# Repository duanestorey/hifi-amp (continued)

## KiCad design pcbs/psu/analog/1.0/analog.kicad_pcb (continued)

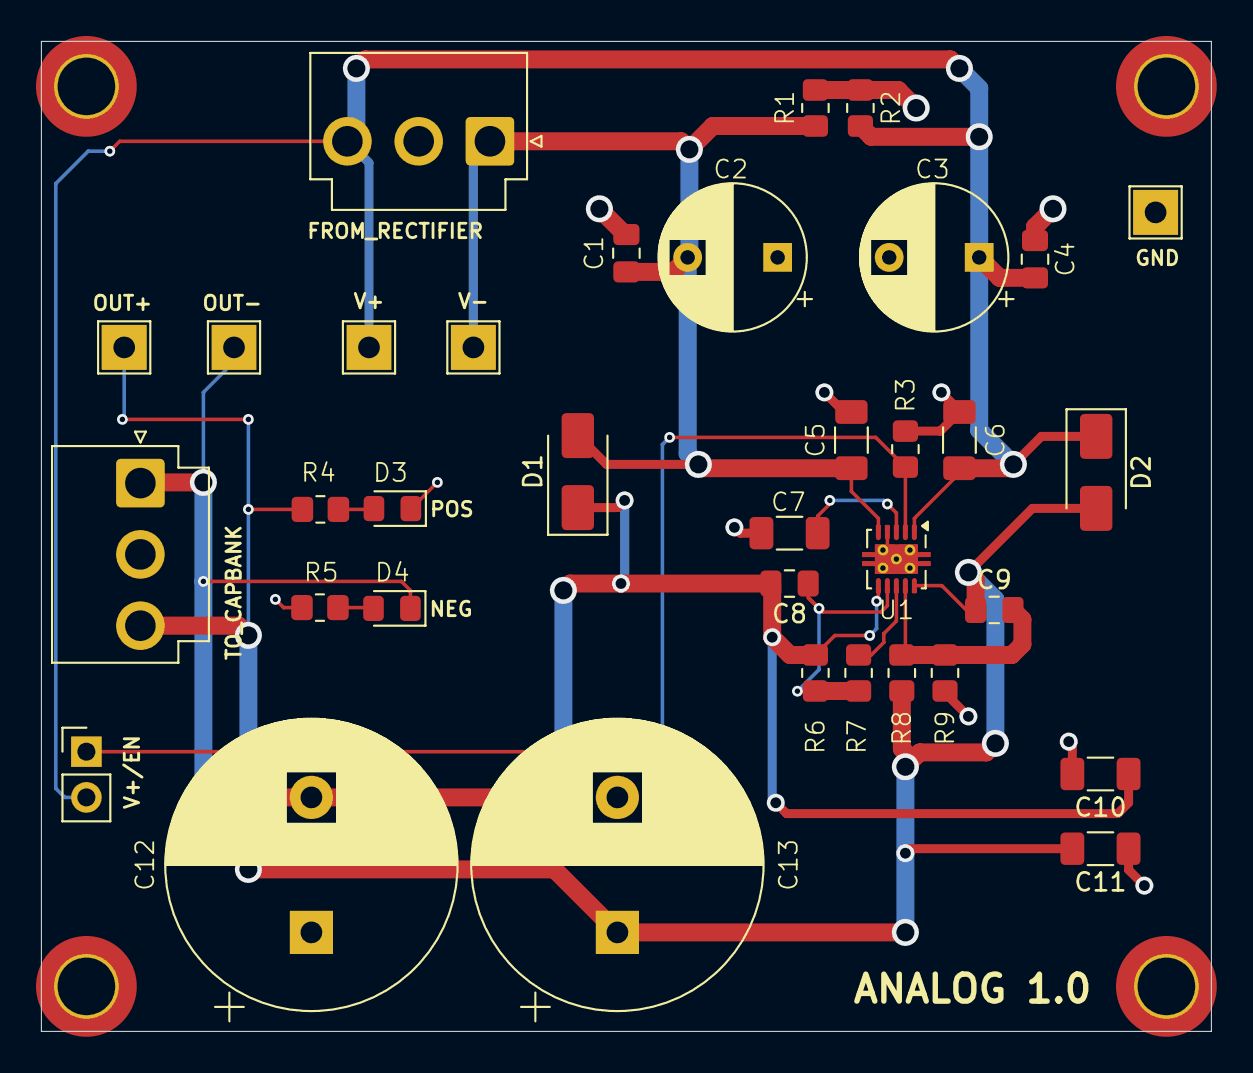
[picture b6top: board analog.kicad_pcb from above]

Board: 2 copper layers, 65.0 x 55.0 mm, 39 parts (0 on the bottom side), 12 nets.
